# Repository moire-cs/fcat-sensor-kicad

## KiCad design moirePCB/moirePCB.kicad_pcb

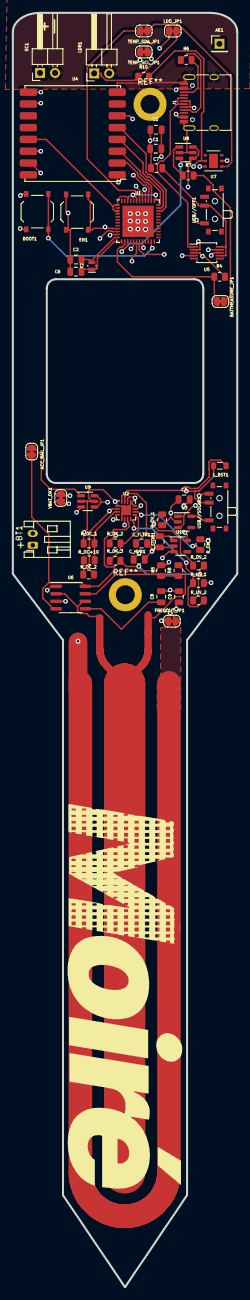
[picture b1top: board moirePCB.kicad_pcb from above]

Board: 4 copper layers, 38.0 x 215.8 mm, 55 parts (0 on the bottom side), 55 nets.

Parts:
ACC_RAIL_JP1: SolderJumper_2_Bridged; SolderJumper-2_P1.3mm_Bridged_RoundedPad1.0x1.5mm
AE1: T1-915M Antenna; PinHeader_1x01_P2.54mm_Vertical
BATTMEASURE_JP1: SolderJumper_2_Bridged; SolderJumper-2_P1.3mm_Bridged_RoundedPad1.0x1.5mm
BOOT1: SW_Push; SW_Push_1P1T_XKB_TS-1187A
BT1: Battery_Cell; JST_PH_S2B-PH-K_1x02_P2.00mm_Horizontal
C1: .1u; C_0805_2012Metric
C2, C6: 12pF/50V; C_0805_2012Metric
C3: .01uF; C_0805_2012Metric
C5: 10u; C_0805_2012Metric
C7: 100nF; C_0805_2012Metric
C8: 10n; C_0805_2012Metric
C9: 100n; C_0805_2012Metric
C_FLTR1: .1uF; C_0805_2012Metric
C_HVR1: 4.7uF; C_0805_2012Metric
C_STOR1: 4.7uF; C_0805_2012Metric
EN1: SW_Push; SW_Push_1P1T_XKB_TS-1187A
FREQOUT_JP1: SolderJumper_2_Bridged; SolderJumper-2_P1.3mm_Bridged_RoundedPad1.0x1.5mm
J1: USB_C_Receptacle; USB_C_Receptacle_HRO_TYPE-C-31-M-12
LDO_JP1: SolderJumper_2_Bridged; SolderJumper-2_P1.3mm_Bridged_RoundedPad1.0x1.5mm
LDR1: R_Photo 50k-100k; PinHeader_1x02_P2.54mm_Horizontal
L_BST1: 22uH; L_0805_2012Metric
R4: 270k; R_0805_2012Metric
R5: 10k; R_0805_2012Metric
R6: 5.1k; R_0805_2012Metric
R7: 820k; R_0805_2012Metric
R8: 1M; R_0805_2012Metric
R10: 360k; R_0805_2012Metric
R_OC+10: 10M; R_0805_2012Metric
R_OC_1: 5.76M; R_0805_2012Metric
R_OC_2: 4.12M; R_0805_2012Metric
R_OK_1: 3.57M; R_0805_2012Metric
R_OK_2: 6.19M; R_0805_2012Metric
R_OK_3: .143M; R_0805_2012Metric
R_OV_1: 4.42M; R_0805_2012Metric
R_OV_2: 5.36M; R_0805_2012Metric
R_UV_1: 3.74M; R_0805_2012Metric
R_UV_2: 6.19M; R_0805_2012Metric
SC1: Solar_Cell; PinHeader_1x02_P2.54mm_Horizontal
TEMP_SCL_JP1: SolderJumper_2_Bridged; SolderJumper-2_P1.3mm_Bridged_RoundedPad1.0x1.5mm
TEMP_SDA_JP1: SolderJumper_2_Bridged; SolderJumper-2_P1.3mm_Bridged_RoundedPad1.0x1.5mm
U1: ESP32-PICO-D4; QFN-48-1EP_7x7mm_P0.5mm_EP5.3x5.3mm
U2: BQ25504; VQFN-16-1EP_3x3mm_P0.5mm_EP1.68x1.68mm
U3, U10: TLV73333PDBV; SOT-23-5
U4: RFM95W-915S2; HOPERF_RFM9XW_SMD
U5: CH340E; MSOP-10_3x3mm_P0.5mm
U6: TLC555xD; SOIC-8_3.9x4.9mm_P1.27mm
U7: HDC1080; Texas_PWSON-N6
U8, U9: AP2281-1WG-7; SOT-23-6
USB//OFF1: SW_DPDT_x2; SW_SPDT_PCM12
USB//SOLAR1: SW_DPDT_x2; SW_SPDT_PCM12
VBAT_OK1: SolderJumper_2_Bridged; SolderJumper-2_P1.3mm_Bridged_RoundedPad1.0x1.5mm
Y2: 32.768kHz; Crystal_SMD_MicroCrystal_CM9V-T1A-2Pin_1.6x1.0mm

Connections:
/D+: J1.A6 (D+), J1.B6 (D+), U5.1 (UD+)
/D-: J1.A7 (D-), J1.B7 (D-), U5.2 (UD-)
/EN: EN1.2, U1.9 (EN), U5.4 (~RTS)
/GPIO_5: U1.34 (IO5), U4.5 (NSS)
/GPIO_12: U1.18 (IO12), U4.15 (DIO1)
/GPIO_13: U1.20 (IO13), U4.14 (DIO0)
/GPIO_14: U1.17 (IO14), U4.6 (RESET)
/GPIO_18: U1.35 (IO18), U4.4 (SCK)
/GPIO_19: U1.38 (IO19), U4.2 (MISO)
/GPIO_21: TEMP_SDA_JP1.2 (B), U1.42 (IO21)
/GPIO_22: TEMP_SCL_JP1.2 (B), U1.39 (IO22)
/GPIO_23: U1.36 (IO23), U4.3 (MOSI)
/RX: U1.40 (U0RXD/IO3), U5.8 (TXD)
/TX: U1.41 (U0TXD/IO1), U5.9 (RXD)
/USB5V: J1.A4 (VBUS), J1.A9 (VBUS), J1.B4 (VBUS), J1.B9 (VBUS), U3.1 (IN), U3.3 (EN)
ACCESSORY_SW: U1.15 (IO26), U8.3 (EN), U9.3 (EN)
A_VCC: ACC_RAIL_JP1.1 (A), C9.1, R5.2, R10.2, U6.4 (R), U6.8 (VCC), U7.5 (VCC)
BATT_MEASURE: BATTMEASURE_JP1.1 (A), R4.2, U1.14 (IO25)
FREQOUT: FREQOUT_JP1.1 (A), U1.10 (IO34)
GND: BOOT1.2, BT1.2 (-), C1.2, C2.1, C3.1, C5.2, C6.2, C7.2, C8.2, C9.2, C_FLTR1.2, C_HVR1.2, C_STOR1.1, EN1.1, J1.A1 (GND), J1.A12 (GND), J1.B1 (GND), J1.B12 (GND), J1.S1 (SHIELD), LDR1.2, R4.1, R_OC_1.1, R_OK_1.2, R_OV_1.1, R_UV_1.2, SC1.2 (-), U1.49 (GND), U2.1 (VSS), U2.5 (OT_PROG), U2.12 (AVSS), U2.13 (VSS), U2.17 (PAD), U3.2 (GND), U4.1 (GND), U4.8 (GND), U4.10 (GND), U5.3 (GND), U6.1 (GND), U7.2 (GND), U8.2 (GND), U8.5 (GND), U9.2 (GND), U9.5 (GND), U10.2 (GND)
LDR_MEASURE: LDO_JP1.1 (A), U1.11 (IO35)
unnamed: ACC_RAIL_JP1.2 (B), U9.1 (OUT)
unnamed: AE1.1 (A), U4.9 (ANT)
unnamed: BATTMEASURE_JP1.2 (B), R7.2
unnamed: BT1.1 (+), U2.14 (VBAT), U8.4 (IN), U8.6 (IN)
unnamed: FREQOUT_JP1.2 (B), U6.3 (Q)
unnamed: J1.A5 (CC1), R6.2
unnamed: J1.B5 (CC2), R6.1
unnamed: LDO_JP1.2 (B), LDR1.1, R10.1
unnamed: R_OC+10.1, R_OC_2.2
unnamed: C_HVR1.1, SC1.1 (+), USB//SOLAR1.3 (C)
unnamed: TEMP_SCL_JP1.1 (A), U7.6 (SCL)
unnamed: TEMP_SDA_JP1.1 (A), U7.1 (SDA)
unnamed: BOOT1.1, U1.23 (IO0)
unnamed: C2.2, U1.12 (IO32), Y2.2
unnamed: C6.1, U1.13 (IO33), Y2.1
unnamed: L_BST1.2, U2.16 (LBST)
unnamed: R_OK_2.2, R_OK_3.1, U2.9 (OK_HYST)
unnamed: R_OK_1.1, R_OK_2.1, U2.10 (OK_PROG)
unnamed: R_OV_1.2, R_OV_2.1, U2.6 (VBAT_OV)
unnamed: R_UV_1.1, R_UV_2.2, U2.8 (VBAT_UV)
unnamed: L_BST1.1, R_OC_2.1, U2.2 (VIN_DC), USB//SOLAR1.2 (B)
unnamed: R_OC+10.2, R_OC_1.2, U2.3 (VOC_SAMP)
unnamed: R_OK_3.2, R_OV_2.2, R_UV_2.1, U2.7 (VRDIV)
unnamed: C3.2, U2.4 (VREF_SAMP)
unnamed: U3.5 (OUT), USB//SOLAR1.1 (A)
unnamed: C7.1, U5.7 (VCC), U5.10 (V3), USB//OFF1.2 (B)
unnamed: C8.1, U6.5 (CV)
unnamed: R5.1, R8.1, U6.7 (DIS)
unnamed: R7.1, U8.1 (OUT)
unnamed: U10.3 (EN), VBAT_OK1.2 (B)
unnamed: C_FLTR1.1, C_STOR1.2, U2.15 (VSTOR), U10.1 (IN)
PROBE: R8.2, U6.2 (TR), U6.6 (THR)
VBAT_OK: U2.11 (VBAT_OK), VBAT_OK1.1 (A)
VCC: C1.1, C5.1, U1.1 (VDDA), U1.3 (VDDA3P3), U1.4 (VDDA3P3), U1.19 (VDD3P3_RTC), U1.37 (VDD3P3_CPU), U1.43 (VDDA), U1.46 (VDDA), U4.13 (3.3V), U9.4 (IN), U9.6 (IN), U10.5 (OUT), USB//OFF1.1 (A)

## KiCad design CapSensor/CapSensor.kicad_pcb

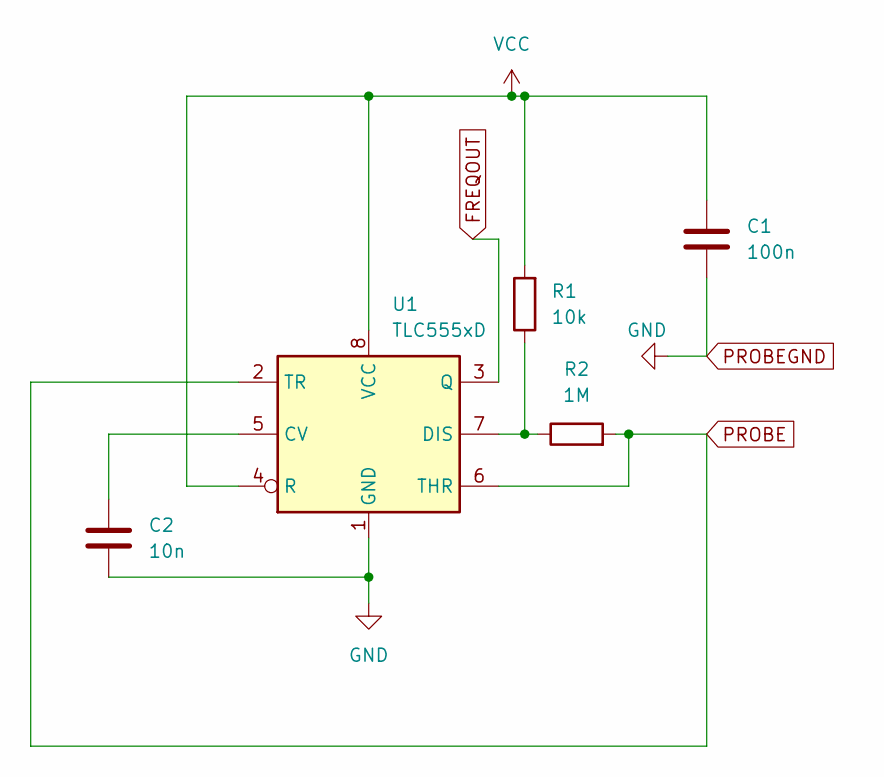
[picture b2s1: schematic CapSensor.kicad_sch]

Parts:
C1: 100n; C_0805_2012Metric
C2: 10n; C_0805_2012Metric
R1: 10k; R_0805_2012Metric
R2: 1M; R_0805_2012Metric
U1: TLC555xD; SOIC-8_3.9x4.9mm_P1.27mm

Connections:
FREQOUT: U1.3 (Q)
unnamed: C2.1, U1.5 (CV)
unnamed: R1.1, R2.1, U1.7 (DIS)
PROBE: R2.2, U1.2 (TR), U1.6 (THR)
PROBEGND: C1.2, C2.2, U1.1 (GND)
VCC: C1.1, R1.2, U1.4 (R), U1.8 (VCC)

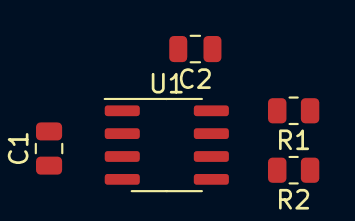
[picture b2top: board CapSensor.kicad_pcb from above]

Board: 2 copper layers, 5 parts (0 on the bottom side), 5 nets.

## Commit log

2023-09-25 initial power schematic
2023-09-29 programmer header
2023-10-05 esp32 and crystal
2023-10-05 new esp
2023-10-07 usb otg
2023-10-16 initial placements
2023-10-16 new placement and battery footprint
2023-10-16 ground plane, routing, comp layout
2023-10-17 vias for esp32
2023-10-17 pcb1 routing
2023-10-19 New Pins
2023-11-12 sensor
2023-11-12 routing wip
2023-11-13 maddie call
2023-11-15 component updates
2023-11-15 layout changes
2023-11-15 new cut outline
2023-11-15 new step file
2023-11-18 pins and jumpers, transistor A_RAIL
2023-11-18 pcb 2 final (submitted to jlc)
2024-02-01 bq25504
2024-02-15 initial pcb 3 layout
2024-02-20 r values needed
2024-02-20 pre route
2024-02-20 resistorValues
2024-02-20 hole battery outline
2024-02-21 rounded bat hole and screw holes
2024-02-22 holed outline v2
2024-02-22 PCB 3
2024-03-19 pcb3 prod
2024-03-19 pcb4: add grounding to esp32
2024-03-19 PCB 4: Silkscreen, part #s
2024-03-19 pcb 4 gerbers
2024-03-19 pcb4: replace rfm95 with correct freq
2024-04-11 pcb-100
2024-04-12 pcb-100-step
